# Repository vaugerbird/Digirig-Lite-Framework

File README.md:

# Digirig-Lite-Framework

Based on v1.2 of the Digirig Lite, with a form factor to fit inside a Framework Expansion card.

PCB Template and future 3D print files from: https://github.com/FrameworkComputer/ExpansionCards

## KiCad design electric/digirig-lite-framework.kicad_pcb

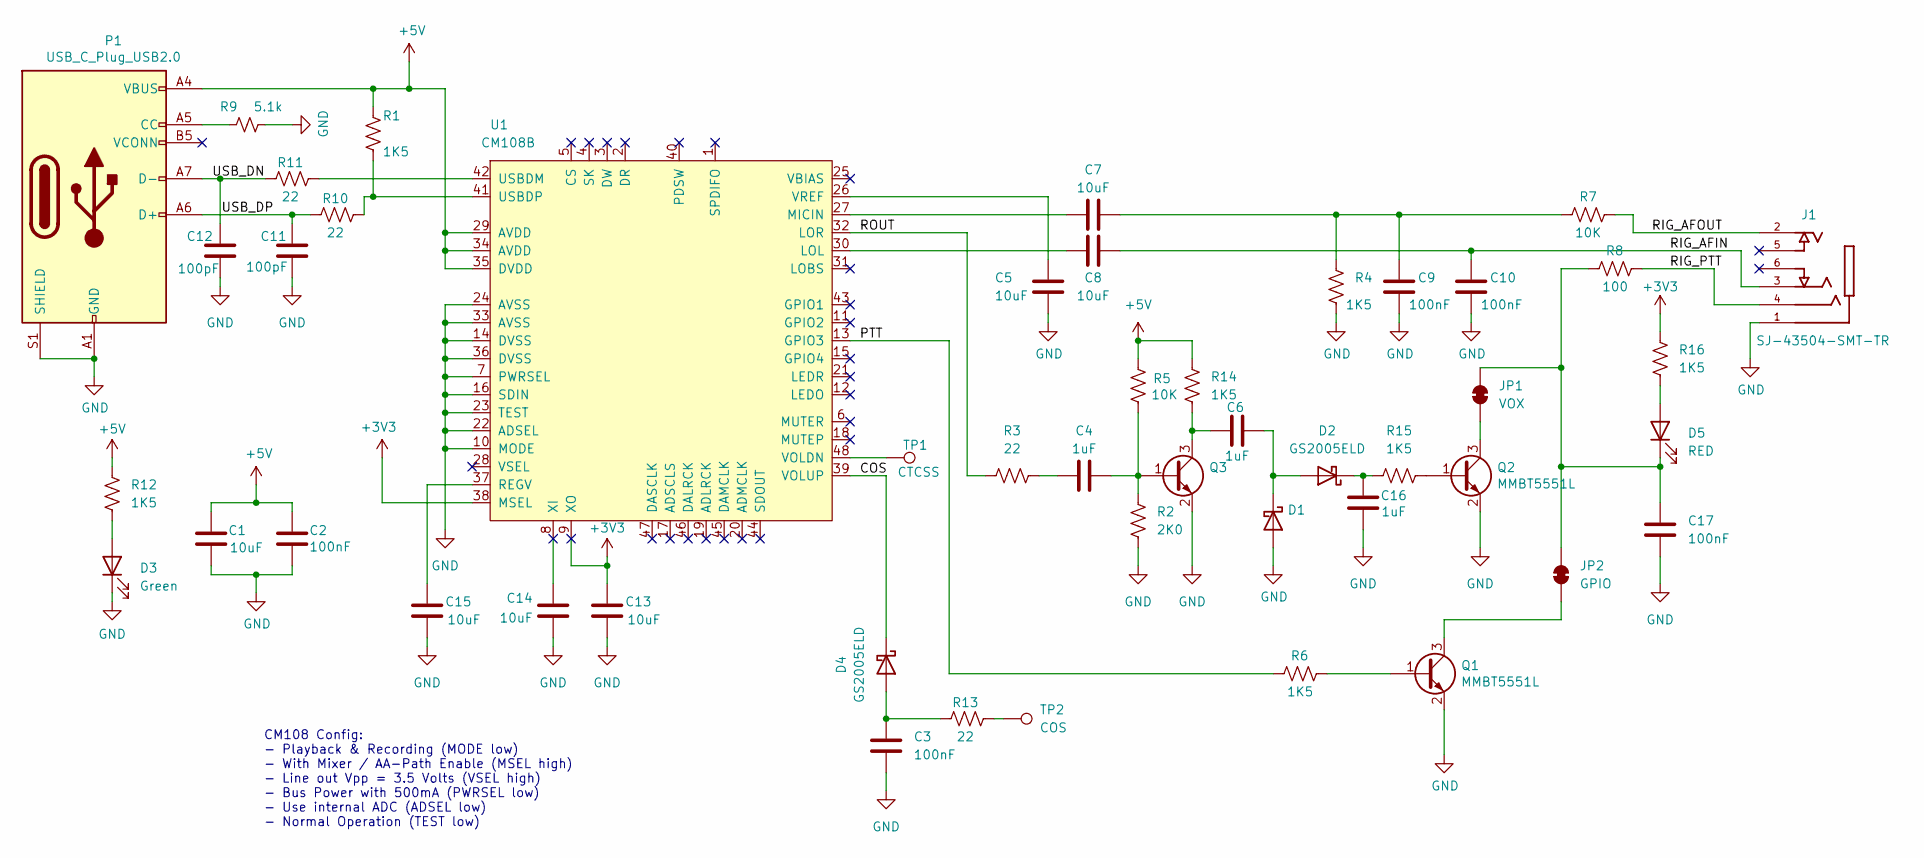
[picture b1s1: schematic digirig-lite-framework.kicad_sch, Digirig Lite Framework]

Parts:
C1, C5, C7, C8, C13, C14, C15: 10uF; C_0402_1005Metric; LCSC C15525
C2, C9, C10: 100nF; C_0402_1005Metric; LCSC C1525
C3, C17: 100nF; C_0402_1005Metric
C4, C6, C16: 1uF; C_0402_1005Metric; LCSC C52923
C11, C12: 100pF; C_0402_1005Metric
D1, D2, D4: GS2005ELD; D_SOD-923; LCSC C18716421
D3: Green; LED_0603_1608Metric
D5: RED; LED_0603_1608Metric
J1: SJ-43504-SMT-TR; CUI_SJ-43504-SMT-TR; PARTREV 10/08/2019
JP1: VOX; SolderJumper-2_P1.3mm_Bridged_RoundedPad1.0x1.5mm
JP2: GPIO; SolderJumper-2_P1.3mm_Bridged_RoundedPad1.0x1.5mm
P1: USB_C_Plug_USB2.0; USB_C_Plug_Molex_105444
Q1, Q2, Q3: MMBT5551L; SOT-23; LCSC C152516
R1, R4, R6: 1K5; R_0402_1005Metric; LCSC C25867
R2: 2K0; R_0402_1005Metric
R3: 22; R_0402_1005Metric; MPN C25092
R5: 10K; R_0402_1005Metric
R7: 10K; R_0402_1005Metric; LCSC C25744
R8: 100; R_0402_1005Metric; LCSC C25867
R9: 5.1k; R_0402_1005Metric
R10, R11, R13: 22; R_0402_1005Metric
R12, R14, R15, R16: 1K5; R_0402_1005Metric
TP1: CTCSS; TestPoint_Pad_D1.5mm
TP2: COS; TestPoint_Pad_D1.5mm
U1: CM108B; LQFP-48_7x7mm_P0.5mm; LCSC C371347

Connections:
+3V3: C13.2, R16.1, U1.9 (XO), U1.38 (MSEL)
+5V: C1.1, C2.1, P1.A4 (VBUS), P1.A9 (VBUS), P1.B4 (VBUS), P1.B9 (VBUS), R1.2, R5.1, R12.1, R14.1, U1.29 (AVDD), U1.34 (AVDD), U1.35 (DVDD)
/COS: D4.1 (K), U1.39 (VOLUP)
/PTT: R6.2, U1.13 (GPIO3)
/RIG_AFIN: C8.1, C10.1, J1.3
/RIG_AFOUT: J1.2, R7.1
/RIG_PTT: J1.4, R8.1
/ROUT: R3.1, U1.32 (LOR)
/USB_DN: C12.1, P1.A7 (D-), R11.2
/USB_DP: C11.1, P1.A6 (D+), R10.2
GND: C1.2, C2.2, C3.2, C5.2, C9.2, C10.2, C11.2, C12.2, C13.1, C14.1, C15.1, C16.2, C17.2, D1.2 (A), D3.1 (K), J1.1, P1.A1 (GND), P1.A12 (GND), P1.B1 (GND), P1.B12 (GND), P1.S1 (SHIELD), Q1.2 (E), Q2.2 (E), Q3.2 (E), R2.2, R4.2, R9.2, U1.7 (PWRSEL), U1.10 (MODE), U1.14 (DVSS), U1.16 (SDIN), U1.22 (ADSEL), U1.23 (TEST), U1.24 (AVSS), U1.33 (AVSS), U1.36 (DVSS)
unnamed: C4.2, R3.2
unnamed: C7.1, C9.1, R4.1, R7.2
unnamed: C6.1, D1.1 (K), D2.2 (A)
unnamed: C16.1, D2.1 (K), R15.1
unnamed: D3.2 (A), R12.2
unnamed: C3.1, D4.2 (A), R13.2
unnamed: D5.2 (A), R16.2
unnamed: C17.1, D5.1 (K), JP1.2 (B), JP2.2 (B), R8.2
unnamed: JP1.1 (A), Q2.3 (C)
unnamed: JP2.1 (A), Q1.3 (C)
unnamed: P1.A5 (CC), R9.1
unnamed: Q1.1 (B), R6.1
unnamed: Q2.1 (B), R15.2
unnamed: C4.1, Q3.1 (B), R2.1, R5.2
unnamed: C6.2, Q3.3 (C), R14.2
unnamed 26: R13.1, TP2.1; also elsewhere on the board
unnamed: C8.2, U1.30 (LOL)
unnamed: C7.2, U1.27 (MICIN)
unnamed: C15.2, U1.37 (REGV)
unnamed: R11.1, U1.42 (USBDM)
unnamed: R1.1, R10.1, U1.41 (USBDP)
unnamed 32: TP1.1, U1.48 (VOLDN); also elsewhere on the board
unnamed: C5.1, U1.26 (VREF)

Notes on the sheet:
CM108 Config: - Playback & Recording (MODE low) - With Mixer / AA-Path Enable (MSEL high) - Line out Vpp = 3.5 Volts (VSEL high) - Bus Power with 500mA (PWRSEL low) - Use internal ADC (ADSEL low) - Normal Operation (TEST low)

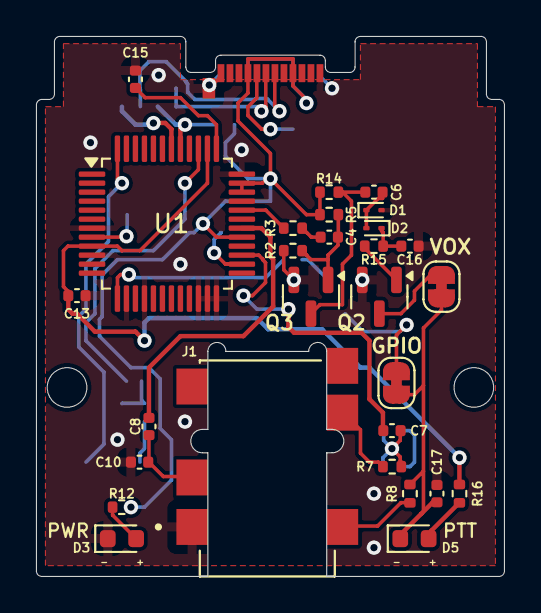
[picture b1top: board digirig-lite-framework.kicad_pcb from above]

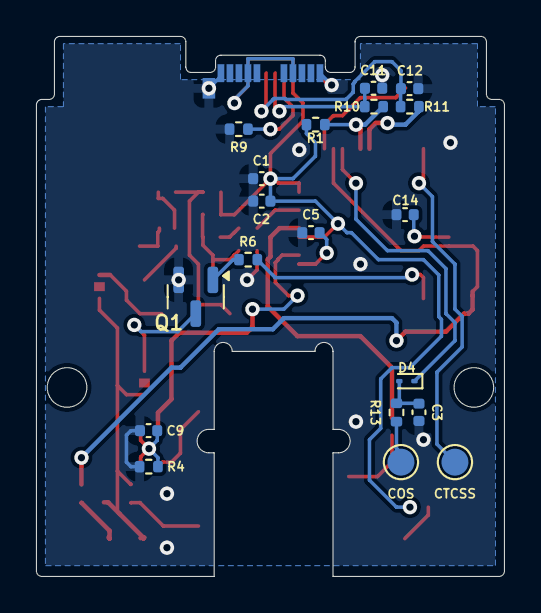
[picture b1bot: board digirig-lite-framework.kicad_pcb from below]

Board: 2 copper layers, 26.0 x 30.0 mm, 50 parts (19 on the bottom side), 34 nets.

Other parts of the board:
COS: COS; TestPoint_Pad_D1.5mm
CTCSS: CTCSS; TestPoint_Pad_D1.5mm
H1, H2: MountingHole; MountingHole_2.2mm_M2

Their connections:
unnamed 26: COS.1; also elsewhere on the board
unnamed 32: CTCSS.1; also elsewhere on the board

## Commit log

2025-02-27 Create v1 board using v1.2 lite schematic

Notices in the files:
electric/digirig-lite-framework.kicad_sch:
GNU General Public License v3.0
